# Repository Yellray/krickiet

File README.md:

# ATtiny85 Cricket

---

## Overview
This project implements a simple audio generator on an ATtiny85 using Timer0 hardware PWM. The firmware drives a piezo output with dynamically modified duty cycles and timing patterns to produce non-periodic, insect-like audio noise.

## Hardware
The circuit is built around an ATtiny85 microcontroller powered directly from a battery. The design is minimal and relies on driving a buzzer directly from the PWM pin, without using a dedicated DAC or any additional analog signal conditioning stage.

## Firmware
Firmware generates a random number to select one of four possible cricket sound patterns. After a pattern is executed, another random value is generated in the range of 25 to 35, which determines the idle time in minutes during which the device does nothing and stays inactive. After this sleep-like dead time, the device wakes up, generates a new sound pattern, and the process repeats continuously.

## Sound
The sound is created by directly changing the PWM output value at irregular moments in time. The sound is a series of short, uneven state changes that together create a rough, insect-like chirping effect.

## Extensions
Sleep modes combined with interrupt-based wake-up can be used to shut the ATtiny85 down completely for long periods, such as around 30 minutes, while maintaining very low power consumption. The device can then wake up using a timer or external interrupt, run its sound routine, and return to sleep again. Based on an estimate, this approach could roughly double the battery life, resulting in around a month of operation depending on the power source and usage pattern.

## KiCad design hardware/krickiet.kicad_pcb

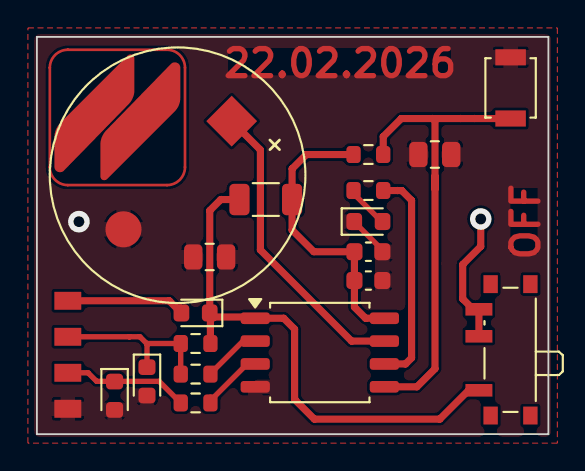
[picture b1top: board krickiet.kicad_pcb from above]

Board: 2 copper layers, 28.4 x 22.1 mm, 20 parts (1 on the bottom side), 12 nets.

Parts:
BT1: Battery_Cell; 1070TR
BZ1: Buzzer; Buzzer_D14mm_H7mm_P10mm
C1, C2: C_Small; C_0603_1608Metric
D1: D; D_0603_1608Metric
D2, D3: D_Zener; D_0603_1608Metric
D4: LED; D_0603_1608Metric
J1: USB; PinHeader_1x04_P1.27mm_Vertical
JP1: Jumper_2_Bridged; R_1206_3216Metric
JP2, JP3: Jumper_2_Bridged; R_0805_2012Metric
R1, R2, R3, R4, R5: R; R_0603_1608Metric
SW1: SW_Nidec_CAS-120A1; SW_SPDT_PCM12
SW2: SW_Push; SW_SPST_B3U-1000P
U1: ATtiny85-20S; SOIC-8_5.3x5.3mm_P1.27mm

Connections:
+3V0: C1.1, C2.1, D1.1 (K), JP1.1 (A), JP1.2 (B), R1.1, R5.1, SW1.1 (C), U1.1 (~RESET/PB5), U1.8 (VCC)
+5V0: D1.2 (A), J1.4
/DN: R2.2, U1.2 (XTAL1/PB3)
/DP: R3.2, U1.3 (XTAL2/PB4)
/FB: R5.2, SW2.1, U1.5 (AREF/PB0)
/KO: BZ1.1 (+), U1.7 (PB2)
/SL: R4.1, U1.6 (PB1)
GND: BT1.2 (-), BZ1.2 (-), C1.2, C2.2, D2.2 (A), D3.2 (A), D4.1 (K), J1.1, JP2.1 (A), JP2.2 (B), JP3.1 (A), JP3.2 (B), SW2.2, U1.4 (GND)
unnamed: BT1.1 (+), SW1.2 (B), SW1.3 (A)
unnamed: D2.1 (K), J1.2, R3.1
unnamed: D3.1 (K), J1.3, R1.2, R2.1
unnamed: D4.2 (A), R4.2

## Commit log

2026-06-24 chore: add files
2026-06-24 chore: add vscode extention files
2026-06-24 docs: add pcb render
2026-06-24 docs: add readme
2026-06-25 docs: update readme title
